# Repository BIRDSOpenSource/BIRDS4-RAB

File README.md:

<div align="center">
  
</div>

# BIRDS4-RAB
 Documentation for the Rear Access Board used in the BIRDS4 satellite

## About the BIRDS4 Program:

The Mission Statement of the Project is:

> “By successfully building and operating first satellite of nation, advance toward indigenous space program in each country”

The project is led by Kyushu Institute of Technology in Japan and involves students from Philippines, Paraguay, Nepal, Turkey and Japan.

Satellite Names: Tsuru (Japan), Guarani-1 (Paraguay) and Maya-2 (Phillipines)

Stakeholders:  Paraguayan Space Agency, Polytechnic Faculty of National University of Asuncion, and Kyushu Institute of Technology (Kyutech) for Japan.

Project duration: 2018-2022

CubeSat: 1U (10x10x10) cm3

Weight: 1.13kg

Launch Date: 21st February 2021 

BIRDS-4 has 1 main missions in total; APRS Store and forward mission

## Organisation structure

```bash

├── .gitattributes
├── B4 RAB FM Partslist.xls
├── LICENSE
├── RAB_v11.brd
├── RAB_v11.sch
├── README.md
├── bot solder layer.PNG
└── top component.PNG

```

## Features

## I like this project, can I help you?
You are welcome 🙂

* Give us a star ⭐
* Watch repository to be notified about updates 👀
* If you will find some errors, report them in Issues 🐞
* Try Birds designs on some real computer and let us know how it worked in Discussions. 💬
* We would greatly appreciate if you would also tell others about this ecosystem, it helps us to improve BIRDS Open Source. Thank you!

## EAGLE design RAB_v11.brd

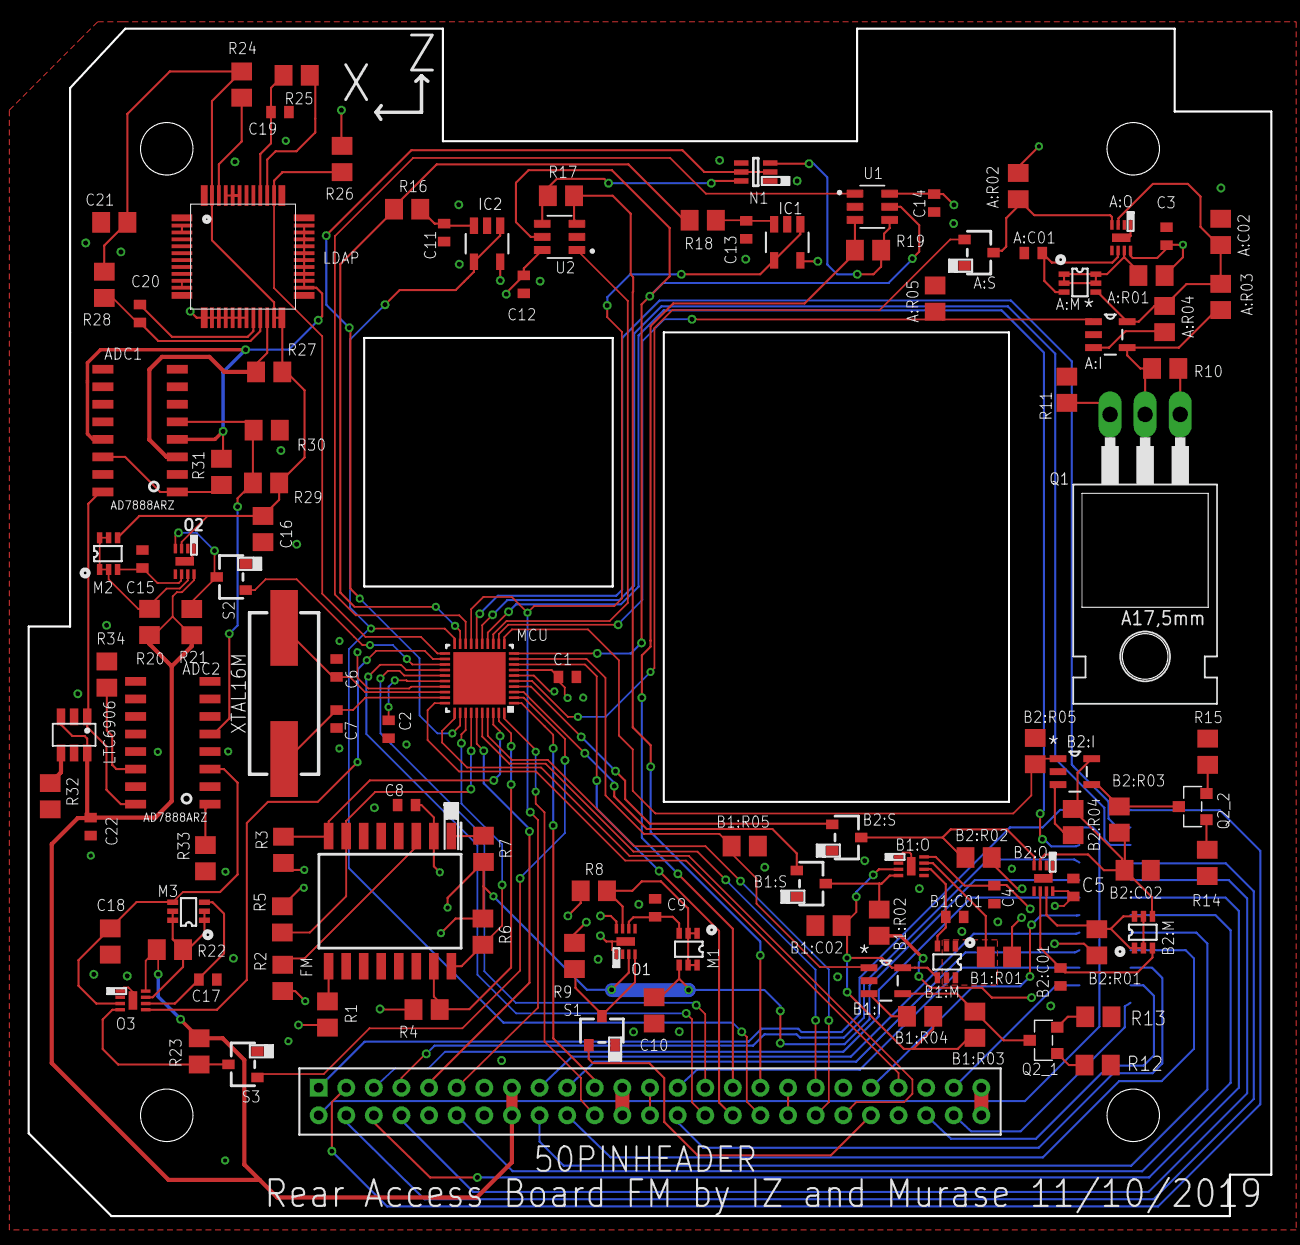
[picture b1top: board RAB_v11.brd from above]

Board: 4 copper layers, 90.0 x 86.0 mm, 115 parts (1 on the bottom side), 120 nets.

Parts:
50PINHEADER: A3B-50PA-2DS(71)
A:C01: 0.1uF; C0402
A:C02: 10uF; C0805
A:I: LT6106HS5PBF; SOT95P280X100-5N
A:M: SSM6K411TU
A:O: LTC4361-2; DFN
A:R01: 0.05Ω; R0805
A:R02: 10kΩ; R0805
A:R03: 10Ω; R0805
A:R04: 100Ω; R0805
A:R05: 1kΩ; R0805
A:S: DTC144EKA; SOT346-R
ADC1: AD7888ARZ
ADC2: AD7888ARZ
B1:C01, B2:C01: 0.1uF; C0402
B1:C02, B2:C02: 10uF; C0805
B1:I, B2:I: LT6106HS5PBF; SOT95P280X100-5N
B1:M, B2:M: SSM6K411TU
B1:O, B2:O: LTC4361-2; DFN
B1:R01, B2:R01: 0.05Ω; R0805
B1:R02, B2:R02: 10kΩ; R0805
B1:R03, B2:R03: 10Ω; R0805
B1:R04, B2:R04: 100Ω; R0805
B1:R05, B2:R05: 1kΩ; R0805
B1:S, B2:S: DTC144EKA; SOT346-R
C1, C2, C3, C4, C5, C9, C11, C12, C13, C14, C15, C17, C22: 0.1uF; C0402
C6, C7: 20pF; C0402
C8: 1uF; C0402
C10, C16, C18, C21: 10uF; C0805
C19: 0.01uF; C0402
C20: 0.047uF; C0402
CLCK: LTC6906
CON-1: RAB_ACCESS
FM: MT25QL01GBBB8ESF-0SIT; SOIC127P1032X265-16N
IC1, IC2: MCP601OT; SOT23-5
LDAP: LQFP-48
M1, M2, M3: SSM6K411TU
MCU: PIC16F1789; UQFN40ML5X5MM
N1: SQ1922EEH; SOT65P210X110-6N
O1, O2, O3: LTC4361-2; DFN
Q1: IRF620; TO220
Q2_1, Q2_2: IRLML5203; MICRO3
R1, R2, R3, R4, R5, R6, R7, R9, R21, R23: 10kΩ; R0805
R8, R20, R27: 0.05Ω; R0805
R10, R12, R14: 1kΩ; R0805
R11, R13, R15: 200Ω; R0805
R16, R18: 2kΩ; R0805
R17, R19: 0.5Ω; R0805
R22: 1Ω; R0805
R24: 2.5MΩ; R0805
R25, R26, R28, R29, R30: 100kΩ; R0805
R31, R32, R33, R34: 1MΩ; R0805
S1, S2, S3: DTC144EKA; SOT346-R
U1, U2: INA181A1IDBVR; SOT95P280X145-6N
XTAL16M: FOXSDLF-160-20

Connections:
A:N$2: A:I.3, A:R04.1
A:N$3: A:C01.1, A:M.3, A:O.6
A:OCP_VCC: A:C02.1, A:I.5, A:M.4, A:O.3, A:R03.1, A:R04.2
A:ON4: A:O.4, A:R02.1, A:S.3
A:SENSE4: A:M.1, A:M.2, A:M.5, A:M.6, A:O.7, A:R01.2
ADCS_ARM_UART_TX_TO_TMCR: 50PINHEADER.43, MCU.30
ADCS_PROG_PIN1: 50PINHEADER.4, CON-1.P$7
ADCS_PROG_PIN2: 50PINHEADER.7, CON-1.P$8
ADCS_PROG_PIN3: 50PINHEADER.8, CON-1.P$9
APRS_PROG_RX: 50PINHEADER.28, CON-1.P$19
APRS_PROG_TX: 50PINHEADER.27, CON-1.P$20
B1:N$2: B1:I.3, B1:R04.1
B1:N$3: B1:C01.1, B1:M.3, B1:O.6
B1:OCP_VCC: B1:C02.1, B1:I.5, B1:M.4, B1:O.3, B1:R03.1, B1:R04.2
B1:ON4: B1:O.4, B1:R02.1, B1:S.3
B1:SENSE4: B1:M.1, B1:M.2, B1:M.5, B1:M.6, B1:O.7, B1:R01.2
B2:N$2: B2:I.3, B2:R04.1
B2:N$3: B2:C01.1, B2:M.3, B2:O.6
B2:OCP_VCC: B2:C02.1, B2:I.5, B2:M.4, B2:O.3, B2:R03.1, B2:R04.2
B2:ON4: B2:O.4, B2:R02.1, B2:S.3
B2:SENSE4: B2:M.1, B2:M.2, B2:M.5, B2:M.6, B2:O.7, B2:R01.2
BCTEMP_IN: 50PINHEADER.9, MCU.35
CAM_DTR: 50PINHEADER.48, CON-1.P$23
CAM_UART_RX0: 50PINHEADER.47, CON-1.P$22
CAM_UART_TX0: 50PINHEADER.46, CON-1.P$21
CLK: ADC1.16:SCLK, ADC2.16:SCLK, CLCK.OUT
DAC_VREF: MCU.10, U1.5, U2.5
GND: 50PINHEADER.13, 50PINHEADER.14, A:C01.2, A:C02.2, A:I.2, A:O.1, A:O.9, A:R05.1, A:S.1, ADC2.4:AGND, ADC2.13:AGND, B1:C01.2, B1:C02.2, B1:I.2, B1:O.1, B1:O.9, B1:R05.1, B1:S.1, B2:C01.2, B2:C02.2, B2:I.2, B2:O.1, B2:O.9, B2:R05.1, B2:S.1, C1.2, C2.2, C3.2, C4.2, C5.2, C6.2, C7.2, C8.2, C9.2, C10.2, C11.2, C12.2, C13.2, C14.2, C15.2, C16.2, C17.2, C18.2, C19.2, C21.2, C22.2, CLCK.GND, CON-1.P$24, FM.10, IC1.2, IC2.2, LDAP.2:VSSBOT, LDAP.3:VSSBOT, LDAP.4:VSSBOT, LDAP.5:VSSBOT, LDAP.6:VSSBOT, LDAP.7:VSSBOT, LDAP.8:VSSBOT, LDAP.9:VSSBOT, LDAP.10:VSSBOT, LDAP.11:VSSBOT, LDAP.13:RTRIM0, LDAP.14:RTRIM1, LDAP.15:RTRIM2, LDAP.16:RTRIM3, LDAP.17:RTRIM1, LDAP.18:RTRIM2, LDAP.19:RTRIM3, LDAP.43:VSSBOT, LDAP.44:EXTLN, LDAP.45:EXTLNEN, MCU.6, MCU.27, N1.1, N1.4, O1.1, O1.9, O2.1, O2.9, O3.1, O3.9, R11.1, R12.2, R13.1, R14.2, R15.1, R30.2, R32.1, R33.1, R34.1, S1.1, S2.1, S3.1, U1.2, U2.2
HALF_VDD: ADC1.5:AIN1, ADC2.5:AIN1, R29.2, R30.1
HNT_PROG_D+: 50PINHEADER.17, CON-1.P$16
HNT_PROG_D-: 50PINHEADER.18, CON-1.P$15
HNT_PROG_DIO: 50PINHEADER.20, CON-1.P$17
HNT_PROG_VBUS: 50PINHEADER.19, CON-1.P$18
HOLD#: FM.1, R7.1
I1-: N1.6, R17.1, U2.4
I2-: N1.3, R19.1, U1.4
ICSPCLK_MISSION_BOSS: CON-1.P$6, MCU.14
ICSPCLK_SFWARD: 50PINHEADER.3, CON-1.P$1
ICSPDAT_MISSION_BOSS: CON-1.P$5, MCU.15
ICSPDAT_SFWARD: 50PINHEADER.2, CON-1.P$4
ICU-CLK: 50PINHEADER.12, CON-1.P$13
ICU_PROG_DIO: 50PINHEADER.41, CON-1.P$14
ICU_PROG_RST: 50PINHEADER.5, CON-1.P$12
ICU_PROG_VCC: 50PINHEADER.6, CON-1.P$11
MAIN_PIC_DIO_TO_MISSION_BOSS: 50PINHEADER.42, S1.2
MAIN_PIC_UART_RX_TO_MISSION_BOSS: 50PINHEADER.22, MCU.40
MAIN_PIC_UART_TX_TO_MISSION_BOSS: 50PINHEADER.21, MCU.1
MISSION_BOSS_DIO_TO_APRS(5V): 50PINHEADER.38, MCU.37
MISSION_BOSS_DIO_TO_HNT(5V): 50PINHEADER.40, MCU.31
MISSION_BOSS_DIO_TO_SF-WARD(3.3V): 50PINHEADER.37, MCU.36
MISSION_BOSS_UART_RX_TO_SF-WARD: 50PINHEADER.29, MCU.25
MISSION_BOSS_UART_TX_TO_SF-WARD: 50PINHEADER.30, MCU.24
unnamed: Q2_1.2, R13.2
unnamed: Q2_1.1, R12.1
unnamed: C13.1, IC1.3, R18.1
unnamed: C11.1, IC2.3, R16.1
unnamed: ADC2.1:CS, R33.2
unnamed: B2:I.4, B2:R03.2, Q2_2.3
unnamed: CLCK.SET, R32.2
unnamed: ADC2.14:DIN, R34.2
unnamed: O3.4, R23.1, S3.3
unnamed: Q2_2.2, R15.2
unnamed: C17.1, M3.3, O3.6
unnamed: ADC1.1:CS, ADC1.14:DIN, R31.1
unnamed: Q2_2.1, R14.1
unnamed: A:I.4, A:R03.2, Q1.2, R10.2
unnamed: Q1.3, R11.2
unnamed: Q1.1, R10.1
unnamed: B1:I.4, B1:R03.2, Q2_1.3
unnamed: LDAP.39:SMODECTL, R25.1
unnamed: C19.1, LDAP.40:_SMODEEN, R25.2
unnamed: M3.1, M3.2, M3.5, M3.6, O3.7, R22.1
unnamed: C15.1, M2.3, O2.6
unnamed: M2.1, M2.2, M2.5, M2.6, O2.7, R20.1
unnamed: C9.1, M1.3, O1.6
unnamed: LDAP.46:VREF, R24.1
unnamed: C20.1, LDAP.20:EXTCD
unnamed: O2.4, R21.1, S2.3
unnamed: ADC1.3:VDD, LDAP.22:VDDCHIP, R27.1
unnamed: C20.2, LDAP.21:EXTRD, R28.1
NTU(LDAP)_OCP: MCU.23, S2.2
NTU_OCP: MCU.2, S3.2
OCP_V+: C1.1, C2.1, C8.1, C10.1, C12.1, C14.1, CON-1.P$10, FM.2, IC1.5, IC2.5, M1.4, MCU.7, MCU.26, O1.3, R1.2, R2.2, R3.2, R4.2, R5.2, R6.2, R7.2, R26.2, U1.6, U2.6
OCP_VCC: ADC2.3:VDD, C18.1, M3.4, O3.3
OCP_VCC(LDAP): C16.1, C21.1, LDAP.23:VDDLDAP, LDAP.24:VDDTOP, LDAP.47:VDDLDAP, M2.4, O2.3, R24.2, R27.2, R28.2, R29.1
OC_MCU: MCU.22, O3.5
ON4: O1.4, R9.1, S1.3
OSC1: C6.1, MCU.28, XTAL16M.1
OSC2: C7.1, MCU.29, XTAL16M.2
PG_MCU: LDAP.38:PG, MCU.21, R26.1
PHOTODIODE: 50PINHEADER.32, MCU.8
PSC1+: 50PINHEADER.34, IC2.1, IC2.4, MCU.20
PSC1-: 50PINHEADER.33, R17.2, U2.3
PSC2+: 50PINHEADER.11, IC1.1, IC1.4, MCU.17
PSC2-: 50PINHEADER.31, R19.2, U1.3
PSC_CONNECT: MCU.32, N1.2, N1.5
PSC_DAC_SIGNAL1: MCU.19, R16.2, R18.2
PSC_ISNS1: MCU.13, U2.1
PSC_ISNS2: MCU.18, U1.1
RESET: FM.3, R2.1
SENSE4: M1.1, M1.2, M1.5, M1.6, O1.7, R8.2
SPI_CS: FM.7, MCU.34, R5.1
SPI_MISO: FM.8, MCU.38, R3.1
SPI_MOSI: FM.15, MCU.39, R4.1
SPI_SCK: FM.16, MCU.33, R6.1
SUP_3V3_1: 50PINHEADER.25, 50PINHEADER.26
SUP_UNREG_1: 50PINHEADER.23, 50PINHEADER.24
SUP_UNREG_2: 50PINHEADER.35, 50PINHEADER.36
TMCR_I1: B1:I.1, B1:R05.2, MCU.9
TMCR_I2: B2:I.1, B2:R05.2, MCU.11
TMCR_I3: A:I.1, A:R05.2, MCU.12
TMCR_OCP_D1: B1:S.2, MCU.3
TMCR_OCP_D2: B2:S.2, MCU.4
TMCR_OCP_D3: A:S.2, MCU.5
V+: 50PINHEADER.49, 50PINHEADER.50, O1.8, R8.1, R9.2
VCC: 50PINHEADER.15, 50PINHEADER.16, A:O.8, A:R01.1, A:R02.2, B1:O.8, B1:R01.1, B1:R02.2, B2:O.8, B2:R01.1, B2:R02.2, C3.1, C4.1, C5.1, C22.1, CLCK.DIV, CLCK.V+, O2.8, O3.8, R20.2, R21.2, R22.2, R23.2
VPP/!MCLR!_MISSION_BOSS: CON-1.P$3, MCU.16
VPP/!MCLR!_SFWARD: 50PINHEADER.1, CON-1.P$2
VSSCHIP: ADC1.4:AGND, ADC1.13:AGND, LDAP.26:VSSCHIP, LDAP.27:VSSCHIP, LDAP.28:VSSCHIP, LDAP.29:VSSCHIP, LDAP.30:VSSCHIP, LDAP.31:VSSCHIP, LDAP.32:VSSCHIP, LDAP.33:VSSCHIP, LDAP.34:VSSCHIP, LDAP.35:VSSCHIP, R31.2
W#: FM.9, R1.1
